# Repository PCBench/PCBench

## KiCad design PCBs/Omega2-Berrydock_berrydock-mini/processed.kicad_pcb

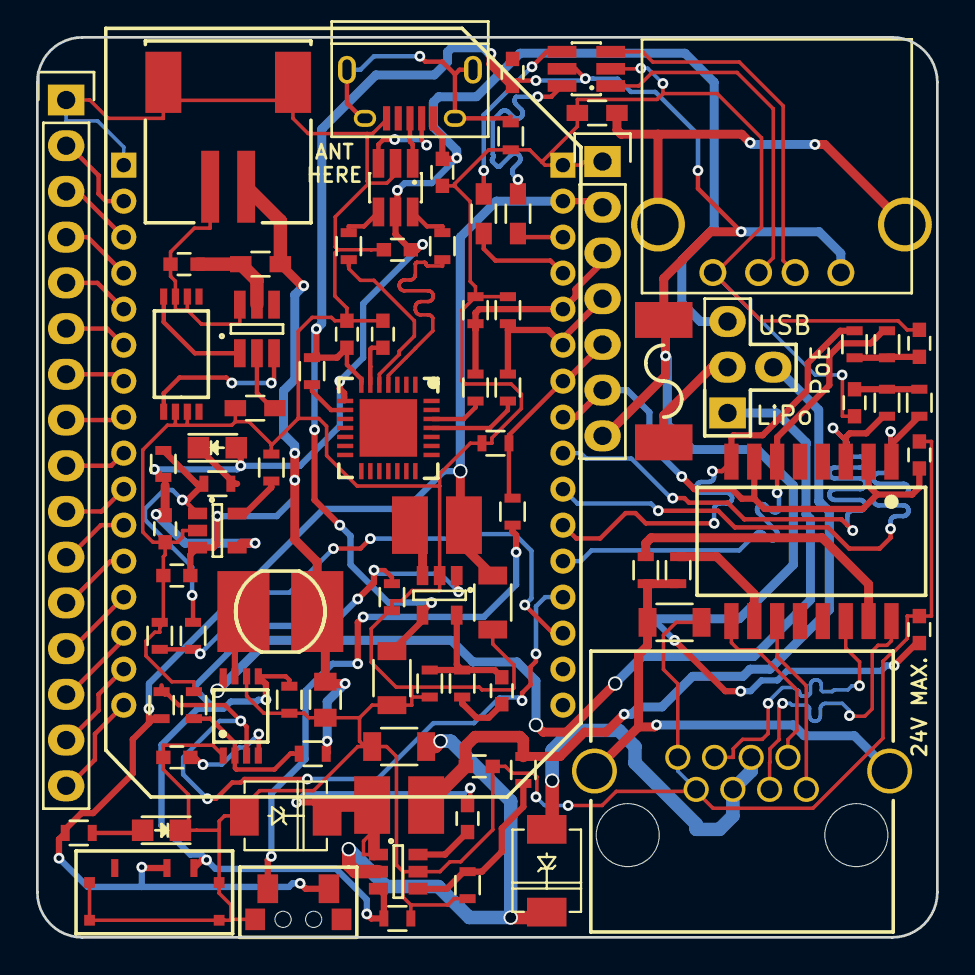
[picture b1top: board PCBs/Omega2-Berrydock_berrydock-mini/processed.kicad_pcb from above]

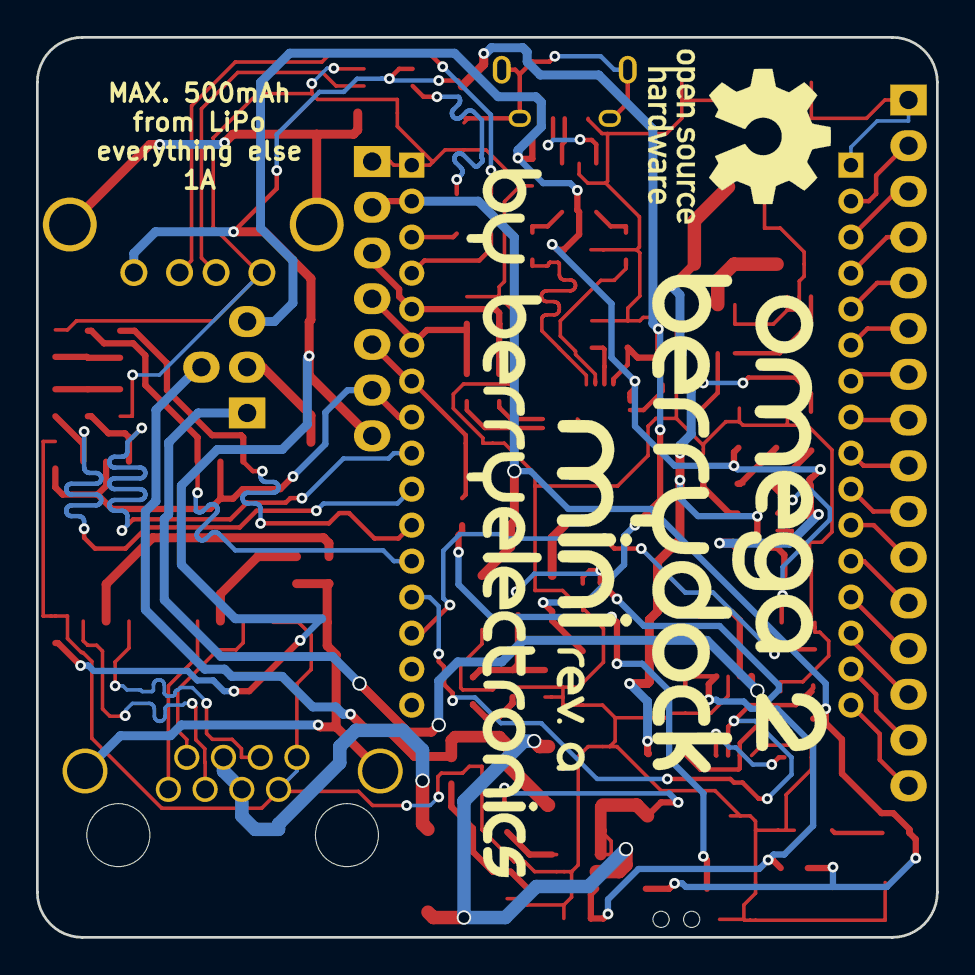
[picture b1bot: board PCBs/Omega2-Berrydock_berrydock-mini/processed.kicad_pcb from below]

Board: 2 copper layers, 50.0 x 50.0 mm, 88 parts (2 on the bottom side), 82 nets.

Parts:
C1, C7: 10uF; C_1206
C4, C5, C12, C15, C19, C20, C21: 100nF; C_0603
C6, C13: 22nF; C_0603
C8, C18: 1uF; C_0603
C9: 1nF/2kV; C_1206
C10: 10uF/50V; C_1206
C11, C14, C17, C22, C23: 4.7uF; C_0603
C16: 47uF; C_0805
D1, D4: Led_Small; LED_0805
D2: 1N4007-SMD; DO-214AC.SMA
D3: B240A; DO-214AC.SMA
F1: 1A/8V; FUSE-1812
G1: SIMPLELOGO; simplelogo
G2: OSHWLOGO; oshwlogo
J1: RJ45; RJ45-SHIELDED
L1: 4.7uH/1A; CD32
L2: 4.7uH; CD32
L3: 10uH; CD43
P1: CONN_01X16; Pin_Header_Straight_1x16
P2: CONN_01X07; Pin_Header_Straight_1x07
P3: CONN_01X04; PWR-SELECT
P4: CONN_01X03; JST-RIGHT-ANGLE
P5: USB_OTG; USB_Micro-B
P6: USB_A
R1, R4, R5, R13, R15, R21, R24, R29: 10K; R_0603
R2, R26, R37, R38: 3K; R_0603
R3, R16, R27, R35, R36: 2K; R_0603
R6, R7, R8, R9: 49.9R; R_0603
R10, R23: 1K; R_0603
R11, R12: 75R; R_0603
R14: 20K; R_0603
R17: 200K; R_0603
R18: 1K; R_0603_HandSoldering
R19: 28.7K; R_0603
R20: 150K; R_0603
R25: 100R; R_0603_HandSoldering
R28: 1M; R_0603
R30, R31: 0R; R_0603_HandSoldering
R32, R33: 0R; R_0603
R34: 1M; R_0603_HandSoldering
SW1: SWITCH_INV; SMD-SLIDESWITCH
SW2: BUTTON; SMD-BUTTON-2x4x3,5
U1: CP2102; QFN-28
U3: TD6811; SOT-23-5
U4: H1260NL; HL1260NL
U5: Omega2; Omega2-Outline
U8: ACT4088; SOT-23-6
U9: MCP73831; SOT-23-5
U10: L6920DC; MSOP8
U11: FS8205A; TSSOP8
U12: DW01-P; SOT-23-6_Handsoldering
U13, U14: USBLC6-2; SOT32-6L

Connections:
+3.3VP: C8.2, P2.6, U4.2, U4.7, U5.25
+3V3: C7.1, L1.2, P2.2, R10.2, R17.1, SW1.2, SW2.1, U5.31
+5P: C14.1, L2.2, P3.2, R20.1
+5V: C1.1, C18.2, C19.2, C23.2, F1.1, P2.7, P6.1, R29.1, U1.7, U3.4, U14.5
+5VD: C11.2, C21.2, C22.2, D4.2, P3.3, P5.1, R21.2, U1.8, U9.4, U13.5
+5VP: P3.1, U10.8
/BAT_-: C15.2, P4.2, U11.2, U11.3, U12.6
/CHRG_STAT: R3.2, R21.1, R23.1, U9.1
/ETH_RX+: R9.2, U4.6, U5.21
/ETH_RX-: R7.2, U4.8, U5.22
/ETH_SHIELD: C9.1, J1.9, R11.1, R12.1
/ETH_TX+: R6.1, U4.1, U5.23
/ETH_TX-: R8.1, U4.3, U5.24
/FW_RST: P2.5, R26.2, R27.1, U5.26
/GPIO0: P1.15, U5.15
/GPIO1: P1.14, U5.14
/GPIO2: P1.4, U5.4
/GPIO3: P1.3, U5.3
/GPIO6: P1.13, U5.13
/GPIO7: P1.12, U5.12
/GPIO8: P1.11, U5.11
/GPIO9: P1.10, U5.10
/GPIO11: P1.2, U5.2
/GPIO15: P1.7, U5.7
/GPIO16: P1.6, U5.6
/GPIO17: P1.5, U5.5
/GPIO45: P1.9, U5.9
/GPIO46: P1.8, U5.8
/LBO: R17.2, U5.20, U10.3
/OC: U11.5, U12.3
/OD: U11.4, U12.1
/PWRON: R1.1, R13.1, R24.1, SW1.1, U3.1, U8.3, U10.5
/RST: P1.16, U5.16
/RX0: P2.3, R35.2, R38.1, U5.28
/RX_R_N: J1.2, U4.9
/RX_R_P: J1.1, U4.11
/TX0: P2.4, R36.1, R37.2, U5.27
/TX_R_N: J1.6, U4.14
/TX_R_P: J1.3, U4.16
/UH_+: R31.2, U5.30
/UH_-: R30.1, U5.29
/UH_R_+: R31.1, U14.6
/UH_R_-: R30.2, U14.4
/UH_S_+: P6.3, U14.1
/UH_S_-: P6.2, U14.3
/USB_+: R33.1, U1.4
/USB_-: R32.2, U1.5
/USB_R_+: R33.2, U13.6
/USB_R_-: R32.1, U13.4
/USB_S_+: P5.3, U13.1
/USB_S_-: P5.2, U13.3
/U_RX: R36.2, U1.25
/U_TX: R35.1, U1.26
GND: C1.2, C4.2, C5.2, C7.2, C8.1, C9.2, C10.2, C11.1, C12.2, C14.2, C16.1, C17.1, C18.1, C20.2, C21.1, C22.1, C23.1, D1.1, D3.2, J1.7, J1.8, P1.1, P2.1, P4.3, P5.5, P6.4, R1.2, R2.2, R4.1, R13.2, R15.2, R16.1, R18.1, R19.1, R24.2, R26.1, R28.2, R34.2, R37.1, R38.2, SW1.4, SW2.3, U3.2, U5.1, U5.32, U8.5, U9.2, U10.1, U10.6, U11.6, U11.7, U13.2, U14.2
unnamed: C4.1, R6.2, R8.2
unnamed: C5.1, R7.1, R9.1
unnamed: C6.1, R4.2, R5.2, U3.5
unnamed: C6.2, R5.1
unnamed: C12.1, U10.4
unnamed: C13.1, U8.6
unnamed: C13.2, D3.1, L2.1, U8.1
unnamed: C15.1, R25.2, U12.5
unnamed: C20.1, U1.6
unnamed: D1.2, R10.1
unnamed: D2.2, J1.4, J1.5
unnamed: D4.1, R23.2
unnamed: F1.2, P3.4
unnamed: L1.1, U3.3
unnamed: L3.1, U10.7
unnamed: P5.6, R28.1
unnamed: P6.5, R34.1
unnamed: R2.1, R3.1, U5.19
unnamed: R11.2, U4.10
unnamed: R12.2, U4.15
unnamed: R14.1, R15.1, U10.2
unnamed: R16.2, U9.5
unnamed: R18.2, U12.2
unnamed: R19.2, R20.2, U8.4
unnamed: R27.2, SW2.2
unnamed: R29.2, U1.9
VDD: C10.1, D2.1, U8.2
VPP: C16.2, C17.2, L3.2, P4.1, R14.2, R25.1, U9.3

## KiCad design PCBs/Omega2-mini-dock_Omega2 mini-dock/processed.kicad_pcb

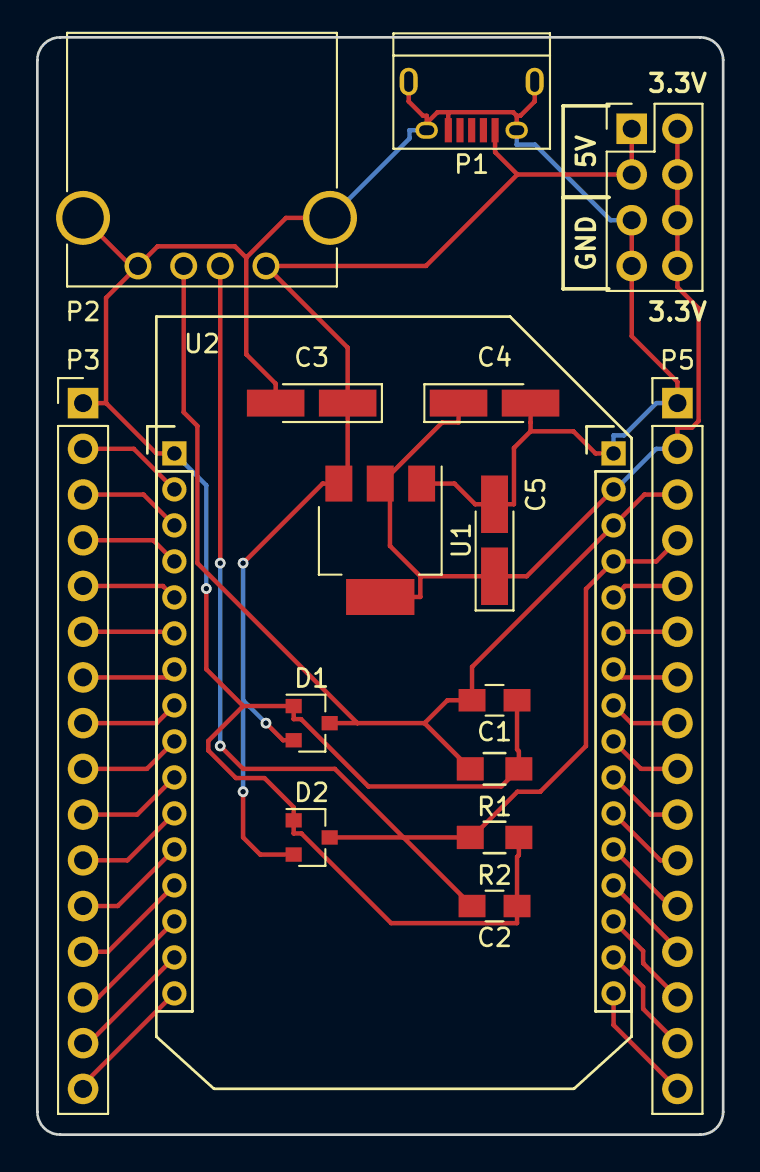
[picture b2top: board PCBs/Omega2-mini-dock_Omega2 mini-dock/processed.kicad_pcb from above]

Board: 2 copper layers, 38.1 x 61.0 mm, 16 parts (0 on the bottom side), 32 nets.

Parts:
C1, C2: 47pF; C_0805_HandSoldering
C3, C4, C5: 100uF; CP_Tantalum_Case-A_EIA-3216-18_Hand
D1, D2: BAT54S; SOT-23
P1: USB_OTG; USB_Micro-B
P2: USB_A
P3, P5: CONN_01X16; Pin_Header_Straight_1x16_Pitch2.54mm
POWER_HDR1: CONN_02X04; Pin_Header_Straight_2x04_Pitch2.54mm
R1, R2: 15k; R_0805_HandSoldering
U1: LM1117-3.3; SOT-223
U2: Omega2

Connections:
3.3VOUT: P5.8, U2.24
+3V3: C4.1, C5.1, P5.2, POWER_HDR1.2, POWER_HDR1.4, POWER_HDR1.6, POWER_HDR1.8, U1.2, U1.4, U2.18
+5V: C3.1, D1.2, D2.2, P1.1, P2.1, POWER_HDR1.1, POWER_HDR1.3, U1.3
CS1: P3.13, U2.13
ETH_RX+: P5.12, U2.28
ETH_RX-: P5.11, U2.27
ETH_TX+: P5.10, U2.26
ETH_TX-: P5.9, U2.25
FW_RESET: P5.7, U2.23
GND: C1.1, C2.1, C3.2, C4.2, C5.2, D1.1, D2.1, P1.5, P1.6, P2.4, P2.5, P3.1, P5.1, POWER_HDR1.5, POWER_HDR1.7, R1.1, R2.1, U1.1, U2.1, U2.17
GPIO11: P3.2, U2.2
GPIO15: P3.7, U2.7
GPIO16: P3.6, U2.6
GPIO17: P3.5, U2.5
GPIO18: P5.13, U2.29
GPIO19: P5.14, U2.30
I2C_SCL: P5.15, U2.31
I2C_SDA: P5.16, U2.32
I2S_CLK: P3.3, U2.3
I2S_SDI: P3.15, U2.15
I2S_SDO: P3.14, U2.14
I2S_WS: P3.4, U2.4
MCU_RESET: P3.16, U2.16
MISO: P3.10, U2.10
MOSI: P3.11, U2.11
SCLK: P3.12, U2.12
UART0_RX: P5.5, U2.21
UART0_TX: P5.6, U2.22
UART1_RX: P3.8, U2.8
UART1_TX: P3.9, U2.9
USB_D+: C1.2, D1.3, P2.3, P5.3, R1.2, U2.19
USB_D-: C2.2, D2.3, P2.2, P5.4, R2.2, U2.20

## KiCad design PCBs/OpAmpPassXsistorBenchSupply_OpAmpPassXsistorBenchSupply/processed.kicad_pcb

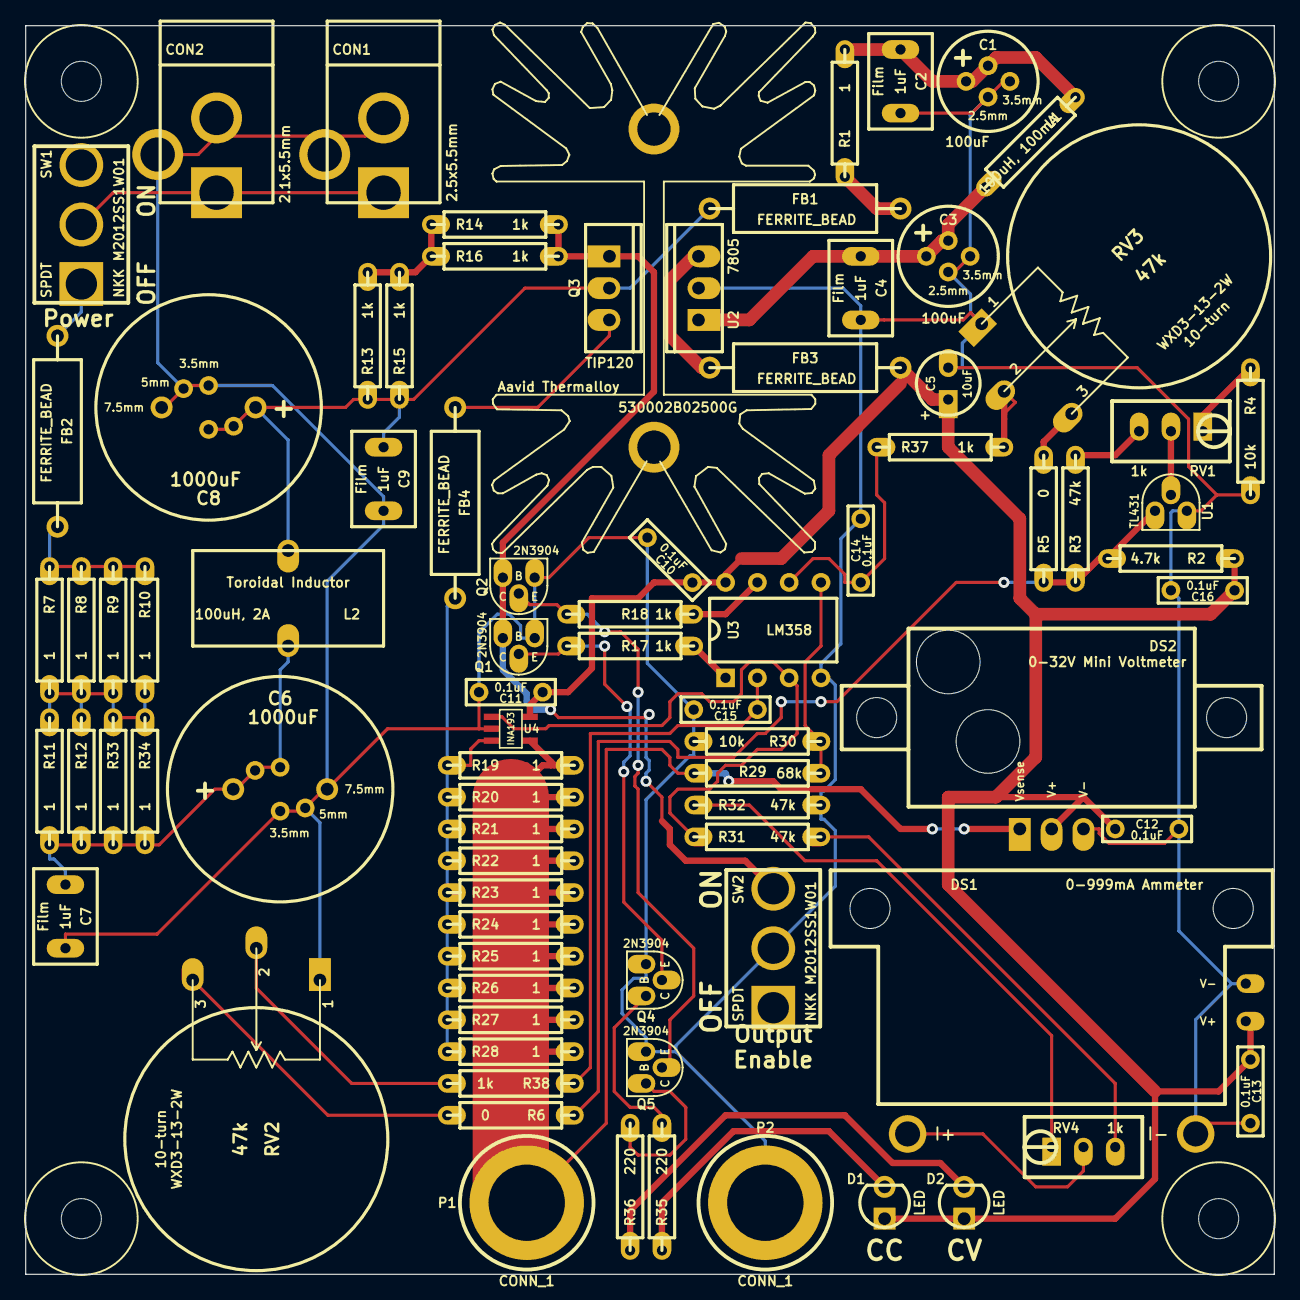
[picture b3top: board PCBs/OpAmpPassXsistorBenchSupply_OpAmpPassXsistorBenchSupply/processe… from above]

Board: 2 copper layers, 99.7 x 99.7 mm, 88 parts (0 on the bottom side), 40 nets.

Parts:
C1, C3: 100uF; MedCap
C2, C4, C7, C9: 1uF; BOXCAP_02_03_02_059C
C5: 10uF; ELCAP_10_20_V_059Bo
C6, C8: 1000uF; BigCap
C10, C11, C12, C13, C14, C15, C16: 0.1uF; CERCAP_2_059A
CON1: 2.5x5.5mm; BARREL_JACK_25x55
CON2: 2.1x5.5mm; BARREL_JACK_21x55
D1, D2: LED; LED_3MM_069A
DS1: AMMETER_V; EBAY_AMMETER
DS2: VOLTMETER; DVM036A
FB1, FB2, FB3, FB4: FERRITE_BEAD; FERRITE_AXIAL_06_069A
H1, H2, H3, H4: HOLE; hole_M3_NPTH
H***: 530002B02500G
L1: 100uH, 100mA; R_AXIAL_0W25_059Bi
L2: 100uH, 2A; Toroid_V_06_03_069Bi
P1, P2: CONN_1; Banana_A
Q1, Q2, Q4, Q5: 2N3904; TO-92_Q_EBC
Q3: TIP120; TO-220_V_069B
R1, R7, R8, R9, R10, R11, R12, R19, R20, R21, R22, R23, R24, R25, R26, R27, R28, R33, R34: 1; R_AXIAL_0W25_059Bi
R2: 4.7k; R_AXIAL_0W25_059Bi
R3, R31, R32: 47k; R_AXIAL_0W25_059Bi
R4, R30: 10k; R_AXIAL_0W25_059Bi
R5, R6: 0; R_AXIAL_0W25_059Bi
R13, R14, R15, R16, R17, R18, R37, R38: 1k; R_AXIAL_0W25_059Bi
R29: 68k; R_AXIAL_0W25_059Bi
R35, R36: 220; R_AXIAL_0W25_059Bi
RV1, RV4: 1k; 3296W
RV2, RV3: 47k; WXD3-13-2W_A
SW1, SW2: SPDT; M2012SS1W01
U1: TL431; TO-92_U_059Bo
U2: 7805; TO-220_V_069B
U3: LM358; DIP8_059A
U4: INA193; SOT23-5

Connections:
/Base: Q1.3, Q2.3, Q3.1, R14.2, R16.2, SW2.3
GND: C1.2, C2.2, C3.2, C4.2, C5.2, C6.2, C7.2, C8.2, C9.2, C10.2, C11.2, C12.2, C13.2, C14.2, C15.2, C16.2, CON1.2, CON1.3, CON2.2, CON2.3, DS1.2, DS1.4, DS2.3, P2.1, Q1.1, Q2.1, Q4.1, Q5.1, R4.2, R30.2, R32.2, RV2.1, RV3.1, SW2.2, U1.3, U2.2, U3.4, U4.2
Icontrol: C15.1, R38.1, U3.2
Isense: R31.1, U3.3, U4.1
unnamed: R5.2, RV3.3
unnamed: R32.1, RV4.1
unnamed: R31.2, RV4.3
unnamed: DS1.1, RV4.2
unnamed: R6.2, RV2.3
unnamed: CON1.1, CON2.1, SW1.2
unnamed: C6.1, C7.1, L2.1, R11.2, R12.2, R33.2, R34.2
unnamed: R7.2, R8.2, R9.2, R10.2, R11.1, R12.1, R33.1, R34.1
unnamed: RV1.2, U1.2
unnamed: FB3.1, U2.3
unnamed: FB4.1, Q3.3
unnamed: FB2.1, SW1.1
unnamed: FB1.2, R1.1
unnamed: R18.2, U3.7
unnamed: R4.1, RV1.1
unnamed: R3.2, RV1.3
unnamed: R17.2, U3.1
unnamed: Q2.2, Q5.2, R18.1
unnamed: Q5.3, R36.2
unnamed: D2.2, R36.1
unnamed: Q4.3, R35.2
unnamed: D1.2, R35.1
unnamed: Q1.2, Q4.2, R17.1
unnamed: R37.2, RV3.2
unnamed: R38.2, RV2.2
unnamed: R13.2, R14.1, R15.2, R16.1
unnamed: C3.1, C4.1, L1.2, U2.1
unnamed: FB2.2, R7.1, R8.1, R9.1, R10.1
unnamed: C1.1, C2.1, L1.1, R1.2
Shunt+: FB4.2, R19.1, R20.1, R21.1, R22.1, R23.1, R24.1, R25.1, R26.1, R27.1, R28.1, U4.3
Shunt-: DS2.1, P1.1, R19.2, R20.2, R21.2, R22.2, R23.2, R24.2, R25.2, R26.2, R27.2, R28.2, R29.1, U4.4
VREF: R2.2, R3.1, R5.1, R6.1, U1.1
Vcc_filt: C8.1, C9.1, FB1.1, L2.2, Q3.2, R13.1, R15.1
Vcc_reg: C5.1, C10.1, C11.1, C12.1, C13.1, C16.1, D1.1, D2.1, DS1.3, DS2.2, FB3.2, R2.1, U3.8, U4.5
Vcontrol: C14.1, R37.1, U3.6
Vsense: R29.2, R30.1, U3.5

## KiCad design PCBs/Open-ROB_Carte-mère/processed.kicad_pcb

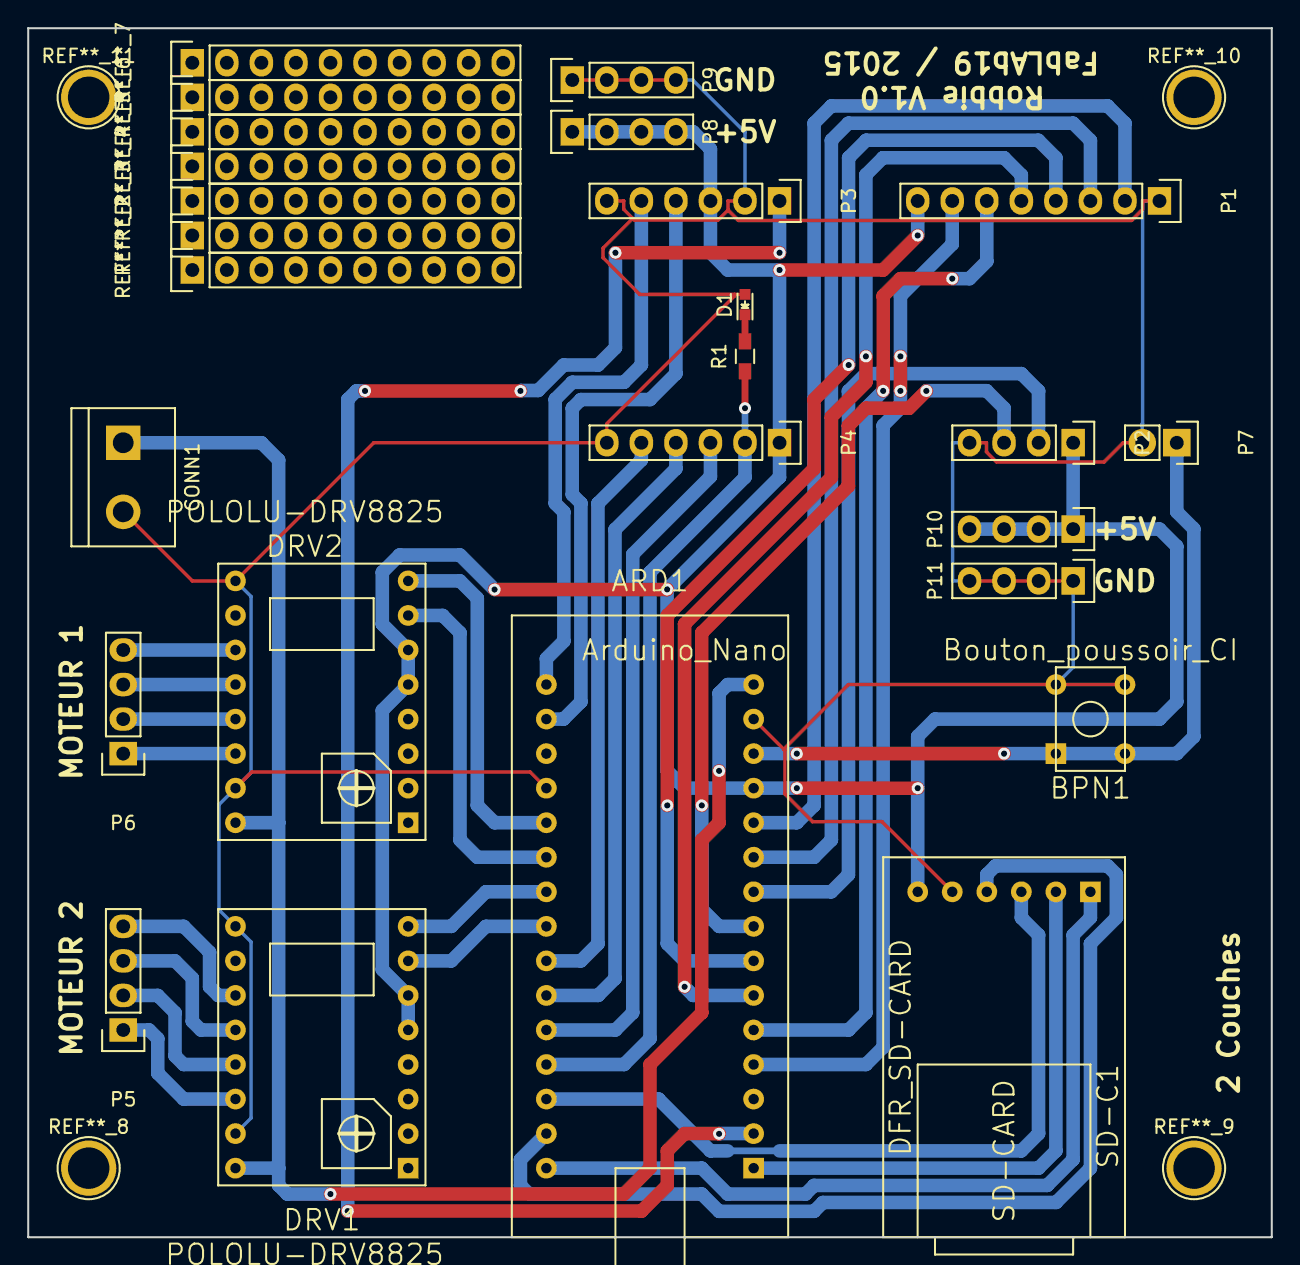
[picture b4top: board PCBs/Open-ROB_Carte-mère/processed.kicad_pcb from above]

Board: 2 copper layers, 91.4 x 88.9 mm, 19 parts (0 on the bottom side), 36 nets.

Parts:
ARD1: Arduino_Nano; Arduino Nano
BPN1: Bouton_poussoir_CI; BPN-CI
CONN1: CONN_2; bornier2
D1: LED; LED-0603
DRV1, DRV2: POLOLU-DRV8825
P1: CONN_01X08; Pin_Header_Straight_1x08
P2, P5, P6, P8, P9, P10, P11: CONN_01X04; Pin_Header_Straight_1x04
P3, P4: CONN_01X06; Pin_Header_Straight_1x06
P7: CONN_01X02; Pin_Header_Straight_1x02
R1: 200; R_0603_HandSoldering
SD-C1: DFR_SD-CARD

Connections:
+3.3V: ARD1.2, P3.1
+5V: ARD1.12, DRV1.5, DRV1.6, DRV2.5, DRV2.6, P1.8, P2.1, P3.3, P4.1, P8.1, P8.2, P8.3, P8.4, P10.1, P10.2, P10.3, P10.4, SD-C1.6
+BATT: ARD1.15, CONN1.1, DRV1.16, DRV2.16
GND: ARD1.14, ARD1.19, BPN1.2, BPN1.4, CONN1.2, D1.2, DRV1.9, DRV1.15, DRV2.9, DRV2.15, P1.1, P2.4, P3.2, P3.6, P4.6, P7.2, P9.1, P9.2, P9.3, P9.4, P11.1, P11.2, P11.3, P11.4, SD-C1.5
unnamed: ARD1.1, SD-C1.2
unnamed: ARD1.4, P1.7
unnamed: ARD1.5, P1.6
unnamed: ARD1.6, P1.5
unnamed: ARD1.7, P1.4
unnamed: ARD1.8, P2.3
unnamed: ARD1.9, P2.2
unnamed: ARD1.10, P1.3
unnamed: ARD1.11, P1.2
unnamed: ARD1.13, BPN1.1, BPN1.3, P7.1
unnamed: ARD1.16, P3.5
unnamed: ARD1.17, P3.4
unnamed: ARD1.20, DRV2.8
unnamed: ARD1.21, DRV2.7
unnamed: ARD1.22, DRV1.8
unnamed: ARD1.23, DRV1.7
unnamed: ARD1.24, P4.5
unnamed: ARD1.25, P4.4
unnamed: ARD1.26, P4.3
unnamed: ARD1.27, P4.2, R1.1
unnamed: ARD1.28, SD-C1.3
unnamed: ARD1.29, SD-C1.4
unnamed: ARD1.30, SD-C1.1
unnamed: D1.1, R1.2
unnamed: DRV1.11, P5.4
unnamed: DRV1.12, P5.3
unnamed: DRV1.13, P5.2
unnamed: DRV1.14, P5.1
unnamed: DRV2.11, P6.4
unnamed: DRV2.12, P6.3
unnamed: DRV2.13, P6.2
unnamed: DRV2.14, P6.1

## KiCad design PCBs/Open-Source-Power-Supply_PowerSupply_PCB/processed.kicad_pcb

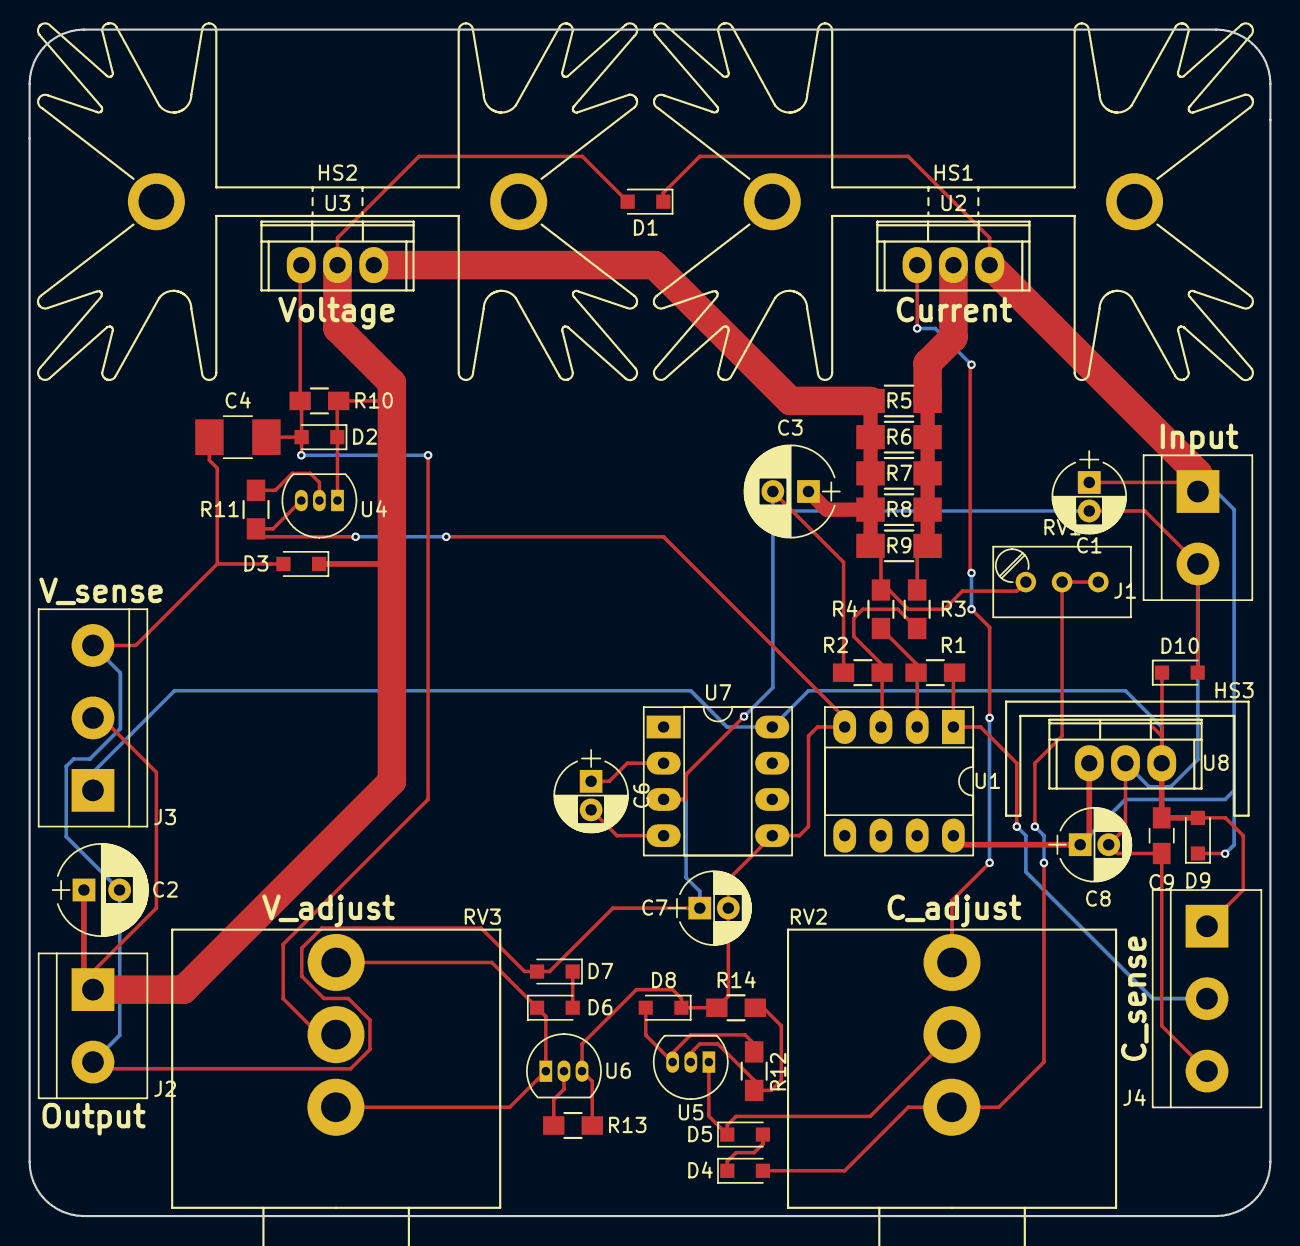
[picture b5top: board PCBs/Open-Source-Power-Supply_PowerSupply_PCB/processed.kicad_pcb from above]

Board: 2 copper layers, 87.0 x 83.2 mm, 50 parts (0 on the bottom side), 23 nets.

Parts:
C1, C6, C7, C8: 10u; CP_Radial_D5.0mm_P2.00mm
C2: 47uF electro; CP_Radial_D6.3mm_P2.50mm
C3: 47u; CP_Radial_D6.3mm_P2.50mm
C4: 4.7u; C_1210_HandSoldering
C9: 0.1u; C_0805_HandSoldering
D1, D2, D3, D9, D10: 1N5819; D_SOD-323_HandSoldering
D4, D5, D6, D7, D8: 1N4448; D_SOD-323_HandSoldering
HS1, HS2: Heatsink; Heatsink_Fischer_SK129-STS_42x25mm_2xDrill2.5mm
HS3: Heatsink; TO220-Small-16mmx8mm
J1: Input Voltage; bornier2
J2: Output Voltage; bornier2
J3: Voltage Meter; bornier3
J4: Current Meter; bornier3
R1, R2: 50k; R_0805_HandSoldering
R3, R4: 10k; R_0805_HandSoldering
R5, R6, R7, R8, R9: 10; R_1206_HandSoldering
R10: 1k; R_0805_HandSoldering
R11, R13: 15; R_0805_HandSoldering
R12: 33; R_0805_HandSoldering
R14: 330; R_0805_HandSoldering
RV1: 100 (multiturn); Potentiometer_Trimmer_Bourns_3296W
RV2, RV3: 10k; Potentiometer-3596S-10k-Pot
U1: LT1013; DIP-8_W7.62mm_Socket_LongPads
U2: LT1086; TO-220
U3: LM1117-ADJ; TO-220
U4, U5, U6: LM334Z; TO-92_Inline_Narrow_Oval
U7: ICL7660; DIP-8_W7.62mm_Socket_LongPads
U8: LM7812CT; TO-220

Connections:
+12V: C9.1, D9.2, D10.1, J3.1, J4.1, U7.8, U8.3
+16V: C1.1, C8.1, D1.1, D9.1, J1.1, U1.8, U2.3, U8.1
-12V: C7.2, D8.1, R11.2, R13.2, R14.2, U1.4, U4.3, U6.3, U7.5
CurrentMeter: J4.2, R1.1, U1.1
GND: C1.2, C2.2, C3.2, C4.2, C7.1, C8.2, C9.2, D3.2, D7.2, D10.2, J1.2, J2.2, J3.3, J4.3, R2.2, U7.3, U8.2
unnamed: C3.1, R4.2, R5.1, R6.1, R7.1, R8.1, R9.1, RV1.1, U3.3
unnamed: C4.1, D2.2, R10.2, RV3.1, U3.1
unnamed: C6.1, U7.2
unnamed: C6.2, U7.4
unnamed: D4.1, D5.2
unnamed: D4.2, RV1.2, RV1.3, RV2.3
unnamed: D5.1, RV2.1, U5.1
unnamed: D6.1, RV3.2, RV3.3, U6.1
unnamed: D6.2, D7.1
unnamed: D8.2, R12.2, U5.3
unnamed: R1.2, R4.1, U1.2
unnamed: R2.1, R3.1, U1.3
unnamed: R3.2, R5.2, R6.2, R7.2, R8.2, R9.2, U2.2
unnamed: R11.1, U4.2
unnamed: R12.1, R14.1, U5.2
unnamed: R13.1, U6.2
unnamed: RV2.2, U2.1
VoltageMeter: C2.1, D1.2, D2.1, D3.1, J2.1, J3.2, R10.1, U3.2, U4.1

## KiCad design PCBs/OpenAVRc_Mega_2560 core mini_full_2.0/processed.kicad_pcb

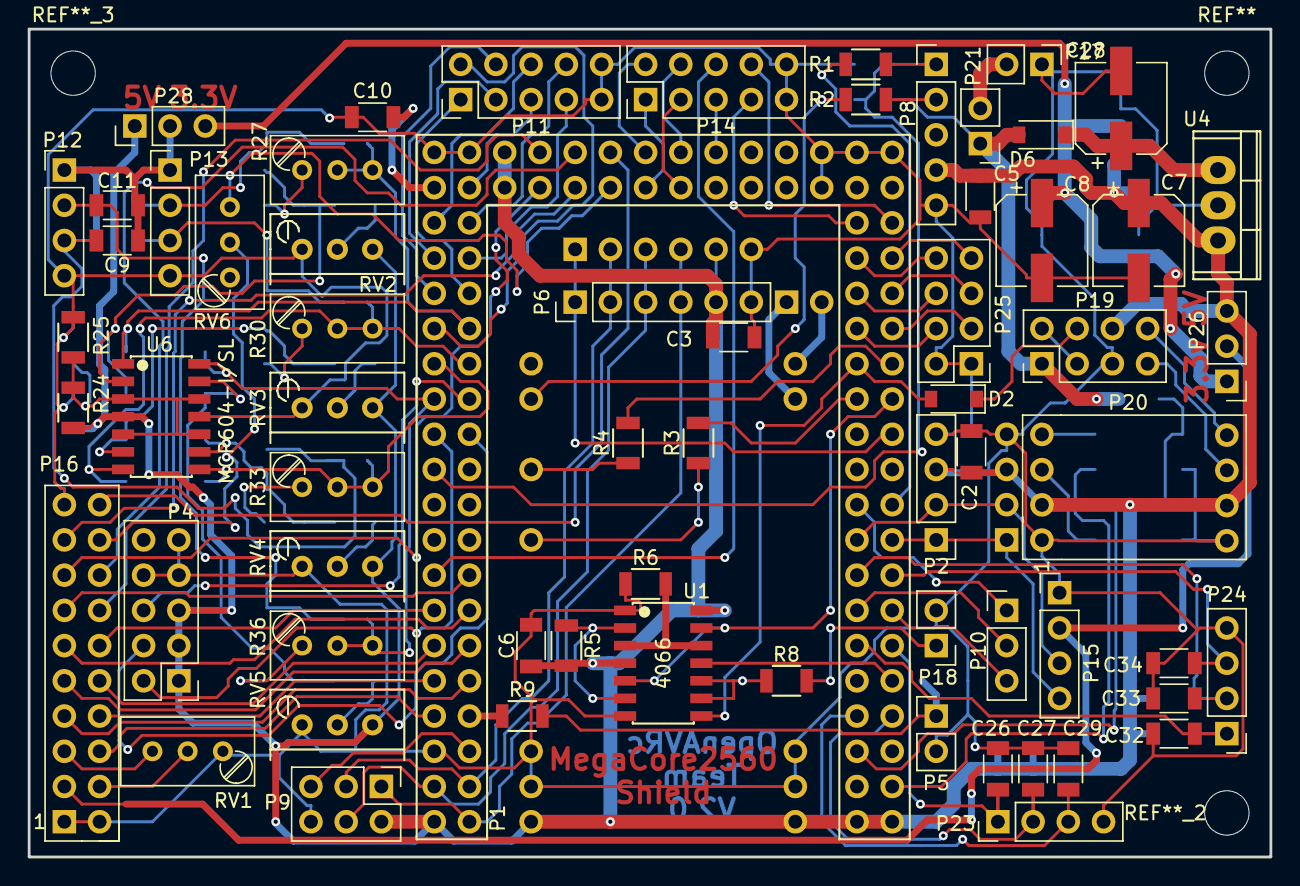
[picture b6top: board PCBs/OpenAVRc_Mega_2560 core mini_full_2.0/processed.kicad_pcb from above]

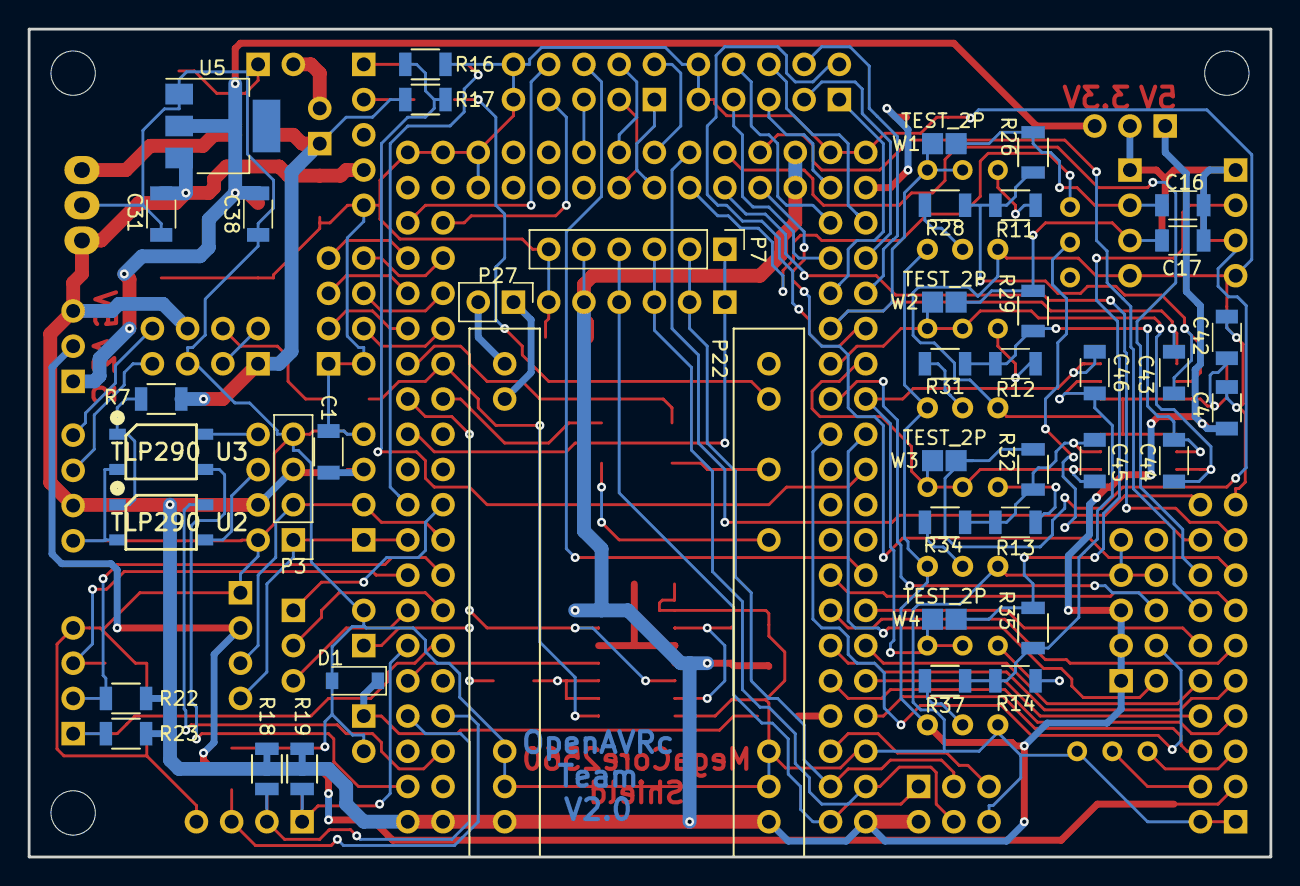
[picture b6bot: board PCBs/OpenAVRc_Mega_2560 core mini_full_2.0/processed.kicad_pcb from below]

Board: 2 copper layers, 89.5 x 59.7 mm, 107 parts (42 on the bottom side), 117 nets.

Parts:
C1, C2, C3, C5: 47nF; C_1206
C4, C6, C9, C10, C11, C16, C17, C26, C27, C29, C31, C32, C33, C34, C38: 100nF; C_1206
C7, C8, C28: 47µF; CP_Elec_6.3x5.3
C42: 6.8nF; C_1206
C43, C44, C45, C46: 22nF; C_1206
D1, D2, D6: MBR0520; D_SOD-123
P1: 2560-core; Connectors-2560-core
P2: Clock; Pin_Header_Straight_1x04_Pitch2.54mm
P3: Option; Pin_Header_Straight_1x04_Pitch2.54mm
P4: Potentiometre; Pin_Header_Straight_2x05_Pitch2.54mm
P5: Vibreur; Pin_Header_Straight_1x02_Pitch2.54mm
P6: Micro_sd; Pin_Header_Straight_1x06_Pitch2.54mm
P7: Option; Pin_Header_Straight_1x06_Pitch2.54mm
P8: Audio; Pin_Header_Straight_1x05_Pitch2.54mm
P9: SPI; Pin_Header_Straight_2x03_Pitch2.54mm
P10: SPI_libre; Pin_Header_Straight_1x03_Pitch2.54mm
P11: Trim; Pin_Header_Straight_2x05_Pitch2.54mm
P12: Stick_left; Pin_Header_Straight_1x04_Pitch2.54mm
P13: Stick_right; Pin_Header_Straight_1x04_Pitch2.54mm
P14: Switch; Pin_Header_Straight_2x05_Pitch2.54mm
P15: LCD_I2C; Pin_Header_Straight_1x04_Pitch2.54mm
P16: LCD; Pin_Header_Straight_2x10_Pitch2.54mm
P17: Battery LIPO; Pin_Header_Straight_1x02_Pitch2.54mm
P18: Ecolage; Pin_Header_Straight_1x02_Pitch2.54mm
P19: Module_TX; Pin_Header_Straight_2x04_Pitch2.54mm
P20: Module_RS232/TTL; Con_RS232_TTL
P21: Sw_power; Pin_Header_Straight_1x02_Pitch2.54mm
P22: CONN_JQ6500_28P_mini; connector_mini-JQ6500-28P
P23: Rot_1; Pin_Header_Straight_1x04_Pitch2.54mm
P24: Rot_2; Pin_Header_Straight_1x04_Pitch2.54mm
P25: Key_select_menu_ESC; Pin_Header_Straight_2x04_Pitch2.54mm
P26: LCD_Vcc_select; Pin_Header_Straight_1x03_Pitch2.54mm
P27: HP; Pin_Header_Straight_1x02_Pitch2.54mm
P28: 5v/3,3v manches; Pin_Header_Straight_1x03_Pitch2.54mm
R1, R2: 22K; R_1206
R3: 18K; R_1206
R4: 1K; R_1206
R5, R6, R26, R28, R29, R31, R32, R34, R35, R37: 10K; R_1206
R7: 470; R_1206
R8: 200; R_1206
R9: 220; R_1206
R11, R12, R13, R14: 15K; R_1206
R16: 2.7K; R_1206
R17: 5.1K; R_1206
R18, R19, R22, R23: 5.1k; R_1206
R24, R25: 33K; R_1206
R27, R30, R33, R36: POT_22k; Potentiometer_Trimmer_Bourns_3296W
RV1: 220K; Potentiometer_Trimmer_Bourns_3296W
RV2, RV3, RV4, RV5: POT_100k; Potentiometer_Bourns_3296W_3-8Zoll_Inline_ScrewUp
RV6: 22K; Potentiometer_Trimmer_Bourns_3296W
U1: 4066; SOP14
U2, U3: TLP290; SOP4
U4: L4941; TO-220
U5: LD1117S33TR; SOT-223
U6: MCP604-I/SL; SOP14
W1, W2, W3, W4: TEST_2P; TESTPT

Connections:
+BATT: D6.2, P19.1, P21.1, R7.1, R17.2
/Isp_rst: P1.RESE, P9.5
/Key_DOWN: P1.49, P25.4
/Key_ESC: P1.44, P25.7
/Key_LEFT: P1.46, P25.5
/Key_MENU: P1.45, P25.8
/Key_RIGHT: P1.47, P25.6
/Key_UP: P1.48, P25.3
/LCD_VCC: P15.2, P16.3, P26.2
/Lcd_A0: P1.D32, P16.16
/Lcd_bla: P1.D35, RV6.3
/Lcd_cs: P1.D34, P16.20
/Lcd_db0: P1.D22, P16.6
/Lcd_db1: P1.D23, P16.7
/Lcd_db2: P1.D24, P16.8
/Lcd_db3: P1.D25, P16.9
/Lcd_db4: P1.D26, P16.10
/Lcd_db5: P1.D27, P16.11
/Lcd_db6: P1.D28, P16.12
/Lcd_db7: P1.D29, P16.13
/Lcd_e: P1.D30, P16.14
/Lcd_r/w: P1.D31, P16.15
/Lcd_rst: P1.D33, P16.17
/Lcd_vo: P16.4, RV1.2
/Microsd_CS: P1.53, P6.1, P7.1
/Miso: P1.MISO, P6.4, P7.4, P9.1
/Mosi: P1.MOSI, P6.3, P7.3, P9.4
/P3_3V: C8.1, C38.1, P26.1, P28.3, U5.2
/PH2: P1.PH2, P10.1
/PPM_TX_OUT: D2.1, P19.4
/PPM_in: P1.PE7, U1.11
/PPM_out: D2.2, P1.PW12, U1.8
/Pot_1: P1.A12, P4.6
/Pot_2: P1.A13, P4.2
/Pot_3: P1.A14, P4.4
/Power_manches: C9.1, C11.1, C16.1, C17.1, P12.1, P13.1, P28.2
/RXD2: P1.D17, P10.3
/RX_module: P19.8, P20.8
/Rot_1A: C29.1, P1.PWD2, P23.3
/Rot_1B: C27.1, P1.PWD3, P23.2, R18.2
/Rot_1push: C26.1, P1.D15, P23.1, R19.2
/Rot_2A: C34.1, P1.D19, P24.3
/Rot_2B: C33.1, P1.D18, P24.2, R22.2
/Rot_2push: C32.1, P1.D14, P24.1, R23.2
/Sck: P1.SCK, P6.2, P7.2, P9.3
/Scl: P1.D21, P2.1, P3.1, P15.4
/Sda: P1.D20, P2.2, P3.2, P15.3
/Sim_control: P1.PW11, U1.5, U1.13
/Stick_LH: C46.1, P1.A11, R36.2, R36.3, U6.14, W4.1
/Stick_LHcon: C9.2, P12.2, R35.2, W4.2
/Stick_LV: C45.1, P1.A9, R33.2, R33.3, U6.8, W3.1
/Stick_LVcon: C11.2, P12.3, R32.2, W3.2
/Stick_RH: C43.1, P1.A8, R27.2, R27.3, U6.1, W1.1
/Stick_RHcon: C16.2, P13.2, R26.2, W1.2
/Stick_RV: C44.1, P1.A10, R30.2, R30.3, U6.7, W2.1
/Stick_RVcon: C17.2, P13.3, R29.2, W2.2
/Sw_ailDR: P1.D38, P14.5
/Sw_eleDR: P1.43, P14.7
/Sw_gear: P1.D40, P14.4
/Sw_id1: P1.D37, P14.1
/Sw_id2: P1.D36, P14.2
/Sw_rudDR: P1.D41, P14.3
/Sw_thcut: P1.D39, P14.6
/Sw_turn: P1.42, P14.8
/TXD2: P1.D16, P10.2
/TX_module: P19.7, P20.7
/Tele_RX: P1.RXD, U3.3
/Tele_TX: P1.TXD, U2.4
/Trim_LH->: P1.A6, P11.1
/Trim_LH<-: P1.A7, P11.2
/Trim_LV->: P1.A4, P11.7
/Trim_LV<-: P1.A5, P11.4
/Trim_RH->: P1.A0, P11.5
/Trim_RH<-: P1.A1, P11.6
/Trim_RV->: P1.A2, P11.8
/Trim_RV<-: P1.A3, P11.3
/U_batt: P1.A15, R16.2, R17.1
/VREF: C10.1, P1.VREF
/Vibreur: P1.PJ7, R9.2
/audio_left_in: P1.PWD6, R1.2
/audio_right_in: P22.DACL, R2.2
/core_pw10: P1.PW10, R3.1
/core_pw13: P1.PW13, R4.1
GND: C1.1, C2.1, C3.1, C4.2, C5.1, C6.2, C7.2, C8.2, C10.2, C26.2, C27.2, C28.2, C29.2, C31.2, C32.2, C33.2, C34.2, C38.2, C42.2, D1.2, P1.GND, P2.4, P3.4, P4.7, P4.8, P4.9, P5.2, P6.6, P7.6, P8.5, P9.6, P11.9, P11.10, P12.4, P13.4, P14.9, P14.10, P15.1, P16.1, P16.2, P16.19, P17.1, P18.2, P19.5, P20.1, P20.5, P22.GND, P23.4, P24.4, P25.1, P25.2, R6.1, R16.1, R25.2, RV1.1, RV2.1, RV3.1, RV4.1, RV5.1, U1.1, U1.7, U2.2, U3.2, U4.2, U5.1, U6.11
unnamed: C28.1, D6.1, U4.1
unnamed: C42.1, R24.2, R25.1, U6.3, U6.5, U6.10, U6.12
unnamed: C43.2, R11.2, R26.1, R28.1, U6.2
unnamed: C44.2, R12.2, R29.1, R31.1, U6.6
unnamed: C45.2, R13.2, R32.1, R34.1, U6.9
unnamed: C46.2, R14.2, R35.1, R37.1, U6.13
unnamed: D1.1, P5.1, R9.1
unnamed: P8.1, R1.1
unnamed: P8.2, R2.1
unnamed: P16.5, RV1.3
unnamed: P16.18, RV6.2
unnamed: P17.2, P21.2
unnamed: P18.1, R8.1
unnamed: P19.2, P19.3
unnamed: P20.3, U2.3
unnamed: P20.4, U3.4
unnamed: P22.BUSY, R3.2
unnamed: P22.RX, R4.2
unnamed: P22.SPK+, P27.2
unnamed: P22.SPK-, P27.1
unnamed: R5.2, U1.2, U1.6
unnamed: R6.2, U1.3, U1.12
unnamed: R7.2, U2.1, U3.1
unnamed: R8.2, U1.9, U1.10
unnamed: R11.1, R27.1
unnamed: R12.1, R30.1
unnamed: R13.1, R33.1
unnamed: R14.1, R36.1
unnamed: R28.2, RV2.2
unnamed: R31.2, RV3.2
unnamed: R34.2, RV4.2
unnamed: R37.2, RV5.2
VCC: C1.2, C2.2, C3.2, C4.1, C5.2, C6.1, C7.1, C31.1, P1.VCC, P2.3, P3.3, P4.1, P4.3, P4.5, P6.5, P7.5, P8.4, P9.2, P19.6, P20.2, P20.6, P22.VCC, P26.3, P28.1, R5.1, R18.1, R19.1, R22.1, R23.1, R24.1, RV2.3, RV3.3, RV4.3, RV5.3, U1.4, U1.14, U4.3, U5.3, U6.4

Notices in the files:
PCBs/Omega2-mini-dock_Omega2 mini-dock/processed.kicad_pcb:
Public Domain
